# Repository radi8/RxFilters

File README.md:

# RxFilters

This is a first iteration of a set of high pass filters for a receiver. The filters are to be used in conjunction with the transmit low pass filters to form a bandpass filter which can be of variable width depending on the HP/LP combination selected. The advantage of this is that the Rx bandwidth can be wide (up to the Tx LP frequency) to enable skimming of frequencies up to the Tx frequency. I will be looking at diode switching of the filters in the future as this will give the option of developing smart filter switching to allow cross band operation etc. The receive can be a band set formed from a HP/LP combination and then when going to Tx the LP filter can be switched to match the Tx frequency and restored on receive.

This version is Relays only.

Notes:
The 1.8 MHz High Pass filter is in circuit by default all the time. In practise the broadcast signals are so strong that they can be received with the filter in. If full sensitivity operation in the broadcast and LF bands is desired then the filter is switched out and any appropriate filter switched in. Also with Hermes-Light the LNA gain can be reduced until clipping stops.

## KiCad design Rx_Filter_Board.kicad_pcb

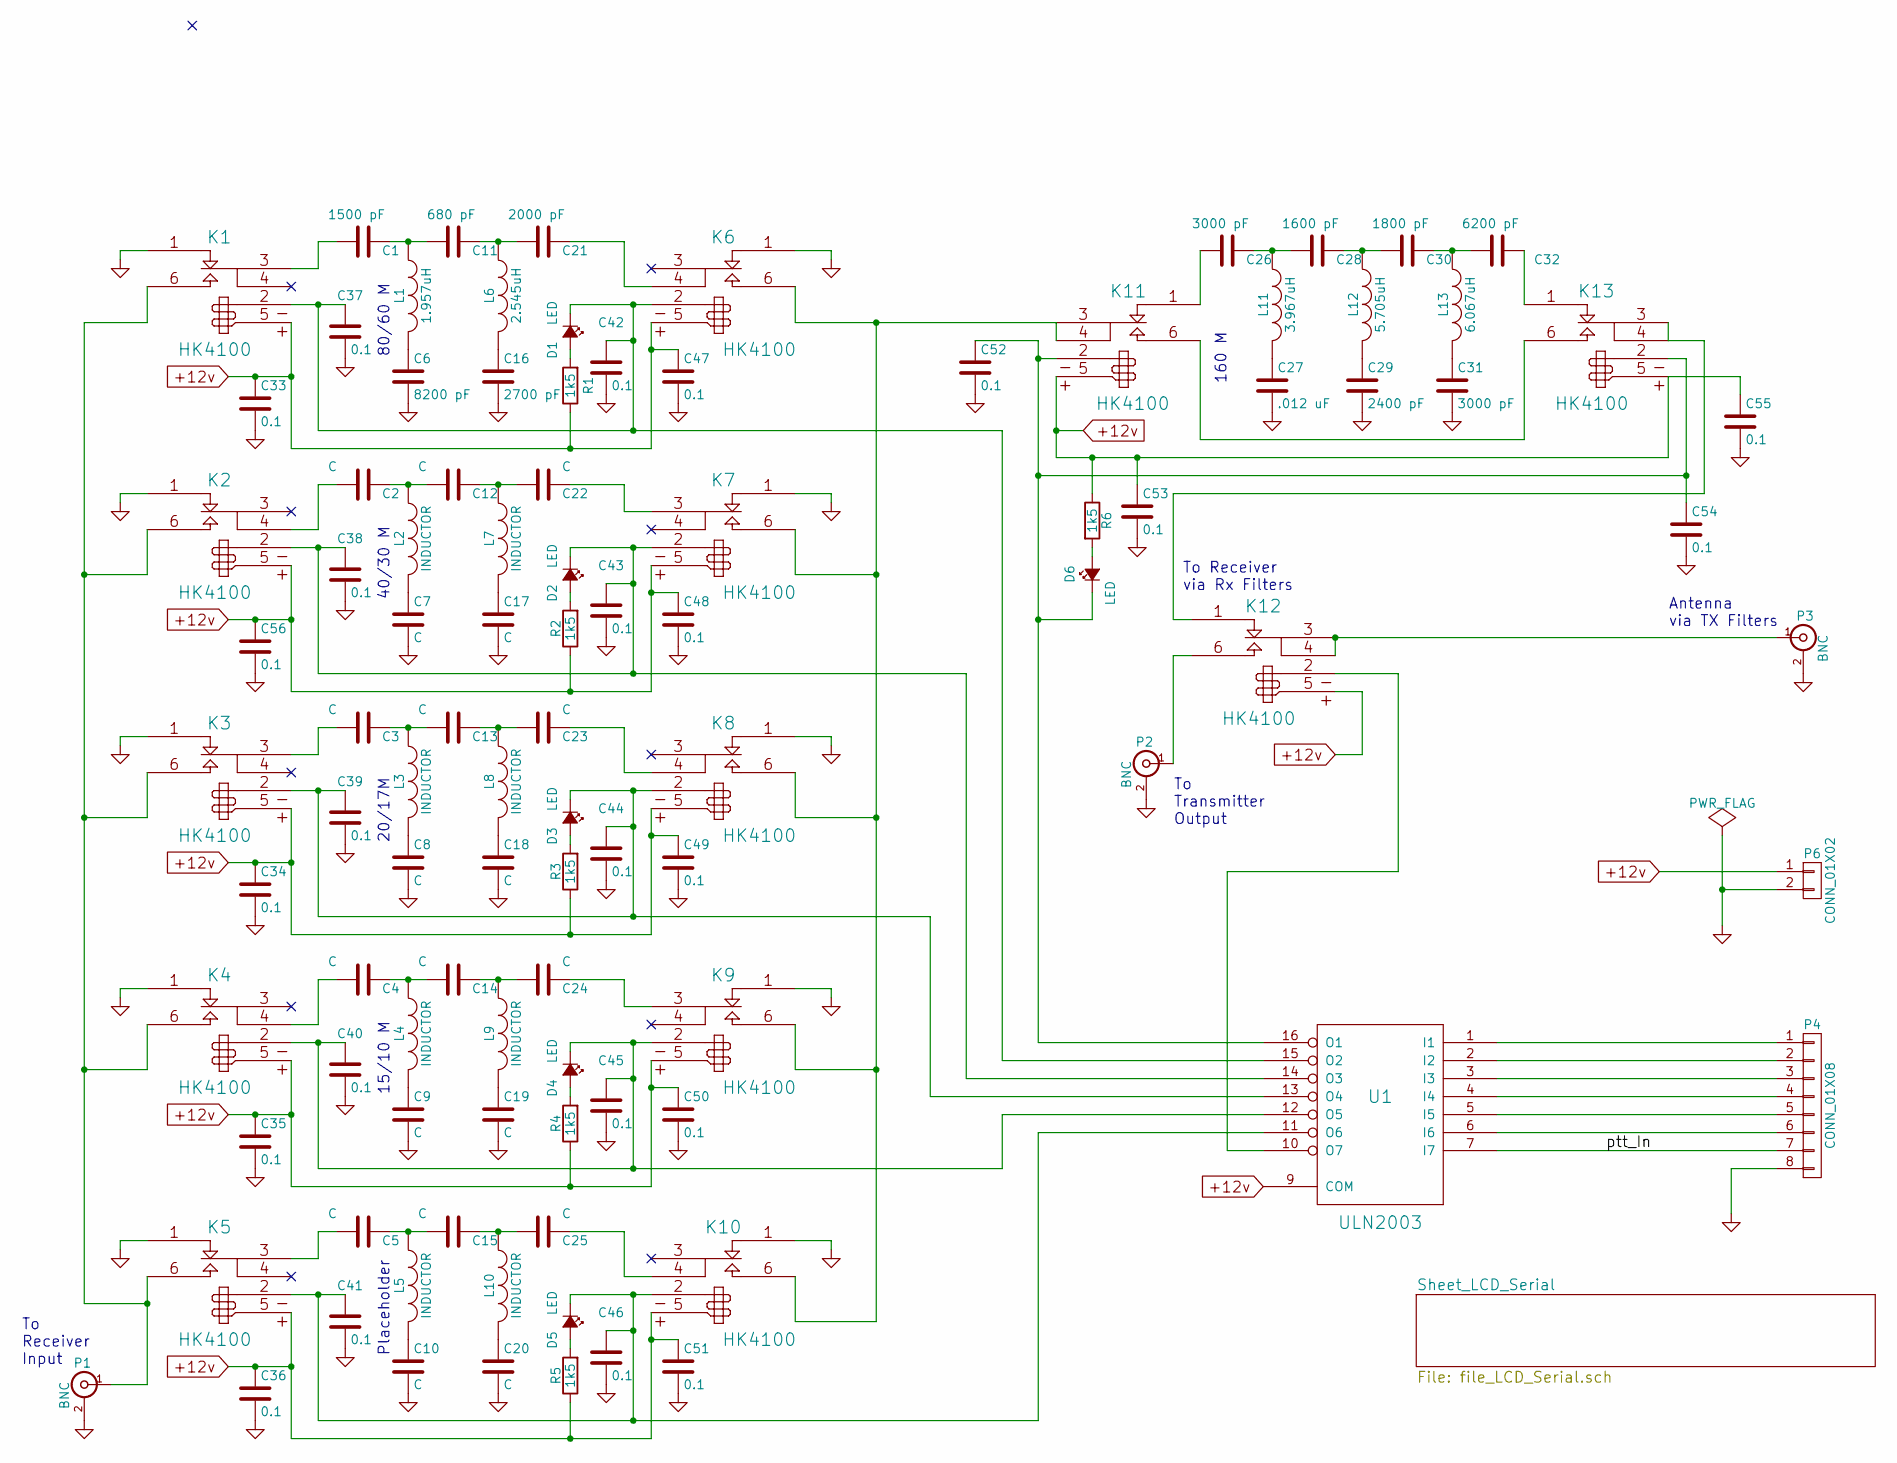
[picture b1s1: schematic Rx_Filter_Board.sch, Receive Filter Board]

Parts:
C1: 1500 pF; C_1206_HandSoldering
C2, C3, C4, C5, C7, C8, C9, C10, C12, C13, C14, C15, C17, C18, C19, C20, C22, C23, C24, C25: C; C_1206_HandSoldering
C6: 8200 pF; C_1206_HandSoldering
C11: 680 pF; C_1206_HandSoldering
C16: 2700 pF; C_1206_HandSoldering
C21: 2000 pF; C_1206_HandSoldering
C26, C31: 3000 pF; C_1206_HandSoldering
C27: .012 uF; C_1206_HandSoldering
C28: 1600 pF; C_1206_HandSoldering
C29: 2400 pF; C_1206_HandSoldering
C30: 1800 pF; C_1206_HandSoldering
C32: 6200 pF; C_1206_HandSoldering
C33, C34, C35, C36, C37, C38, C39, C40, C41, C42, C43, C44, C45, C46, C47, C48, C49, C50, C51, C52, C53, C54, C55, C56: 0.1; C_1206_HandSoldering
D1, D2, D3, D4, D5, D6: LED; LED_1206
K1, K2, K3, K4, K5, K6, K7, K8, K9, K10, K11, K12, K13: HK4100
L1: 1.957uH; Toroid_T37_Vertical
L2, L3, L4, L5, L7, L8, L9, L10: INDUCTOR; Toroid_T37_Vertical
L6: 2.545uH; Toroid_T37_Vertical
L11: 3.967uH; Toroid_T37_Vertical
L12: 5.705uH; Toroid_T37_Vertical
L13: 6.067uH; Toroid_T37_Vertical
P1, P2, P3: BNC; Pin_Header_Straight_1x02
P4: CONN_01X08; Pin_Header_Straight_1x08
P6: CONN_01X02; Pin_Header_Straight_1x02
R1, R2, R3, R4, R5, R6: 1k5; R_1206_HandSoldering
U1: ULN2003; DIP-16_W7.62mm_LongPads

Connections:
+12v: C33.1, C34.1, C35.1, C36.1, C47.1, C48.1, C49.1, C50.1, C51.1, C53.1, C55.1, C56.1, K1.5, K2.5, K3.5, K4.5, K5.5, K6.5, K7.5, K8.5, K9.5, K10.5, K11.5, K12.5, K13.5, P6.1, R1.1, R2.1, R3.1, R4.1, R5.1, R6.1, U1.9 (COM)
/ptt_In: P4.7, U1.7 (I7)
GND: C6.2, C7.2, C8.2, C9.2, C10.2, C16.2, C17.2, C18.2, C19.2, C20.2, C27.2, C29.2, C31.2, C33.2, C34.2, C35.2, C36.2, C37.2, C38.2, C39.2, C40.2, C41.2, C42.2, C43.2, C44.2, C45.2, C46.2, C47.2, C48.2, C49.2, C50.2, C51.2, C52.2, C53.2, C54.2, C55.2, C56.2, K1.1, K2.1, K3.1, K4.1, K5.1, K6.1, K7.1, K8.1, K9.1, K10.1, P1.2 (Ext), P2.2 (Ext), P3.2 (Ext), P4.8, P6.2, U1.8 (GND); also elsewhere on the board
unnamed: C1.1, C11.2, L1.1
unnamed: C1.2, K1.3
unnamed: C2.2, K2.4
unnamed: C3.2, K3.3
unnamed: C4.2, K4.4
unnamed: C5.2, K5.3
unnamed: C6.1, L1.2
unnamed: C7.1, L2.2
unnamed: C8.1, L3.2
unnamed: C9.1, L4.2
unnamed: C10.1, L5.2
unnamed: C11.1, C21.2, L6.1
unnamed: C12.1, C22.2, L7.1
unnamed: C2.1, C12.2, L2.1
unnamed: C13.1, C23.2, L8.1
unnamed: C3.1, C13.2, L3.1
unnamed: C14.1, C24.2, L9.1
unnamed: C4.1, C14.2, L4.1
unnamed: C15.1, C25.2, L10.1
unnamed: C5.1, C15.2, L5.1
unnamed: C16.1, L6.2
unnamed: C17.1, L7.2
unnamed: C18.1, L8.2
unnamed: C19.1, L9.2
unnamed: C20.1, L10.2
unnamed: C21.1, K6.4
unnamed: C22.1, K7.3
unnamed: C23.1, K8.4
unnamed: C24.1, K9.3
unnamed: C25.1, K10.4
unnamed: C26.1, C28.2, L11.1
unnamed: C26.2, K11.1
unnamed: C27.1, L11.2
unnamed: C28.1, C30.2, L12.1
unnamed: C29.1, L12.2
unnamed: C30.1, C32.2, L13.1
unnamed: C31.1, L13.2
unnamed: C32.1, K13.1
unnamed: C37.1, C42.1, D1.1 (K), K1.2, K6.2, U1.15 (O2)
unnamed: C38.1, C43.1, D2.1 (K), K2.2, K7.2, U1.14 (O3)
unnamed: C39.1, C44.1, D3.1 (K), K3.2, K8.2, U1.13 (O4)
unnamed: C40.1, C45.1, D4.1 (K), K4.2, K9.2, U1.12 (O5)
unnamed: C41.1, C46.1, D5.1 (K), K5.2, K10.2, U1.11 (O6)
unnamed: C52.1, C54.1, D6.1 (K), K11.2, K13.2, U1.16 (O1)
unnamed: D1.2 (A), R1.2
unnamed: D2.2 (A), R2.2
unnamed: D3.2 (A), R3.2
unnamed: D4.2 (A), R4.2
unnamed: D5.2 (A), R5.2
unnamed: D6.2 (A), R6.2
unnamed: K1.6, K2.6, K3.6, K4.6, K5.6, P1.1 (In)
unnamed: K6.6, K7.6, K8.6, K9.6, K10.6, K11.3, K11.4
unnamed: K11.6, K13.6
unnamed: K12.1, K13.3, K13.4
unnamed: K12.2, U1.10 (O7)
unnamed: K12.3, K12.4, P3.1 (In)
unnamed: K12.6, P2.1 (In)
unnamed: P4.1, U1.1 (I1)
unnamed: P4.2, U1.2 (I2)
unnamed: P4.3, U1.3 (I3)
unnamed: P4.4, U1.4 (I4)
unnamed: P4.5, U1.5 (I5)
unnamed: P4.6, U1.6 (I6)

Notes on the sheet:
To Receiver via Rx Filters
Antenna via TX Filters
160 M
40/30 M
20/17M
15/10 M
80/60 M
To Receiver Input
To Transmitter Output
Placeholder

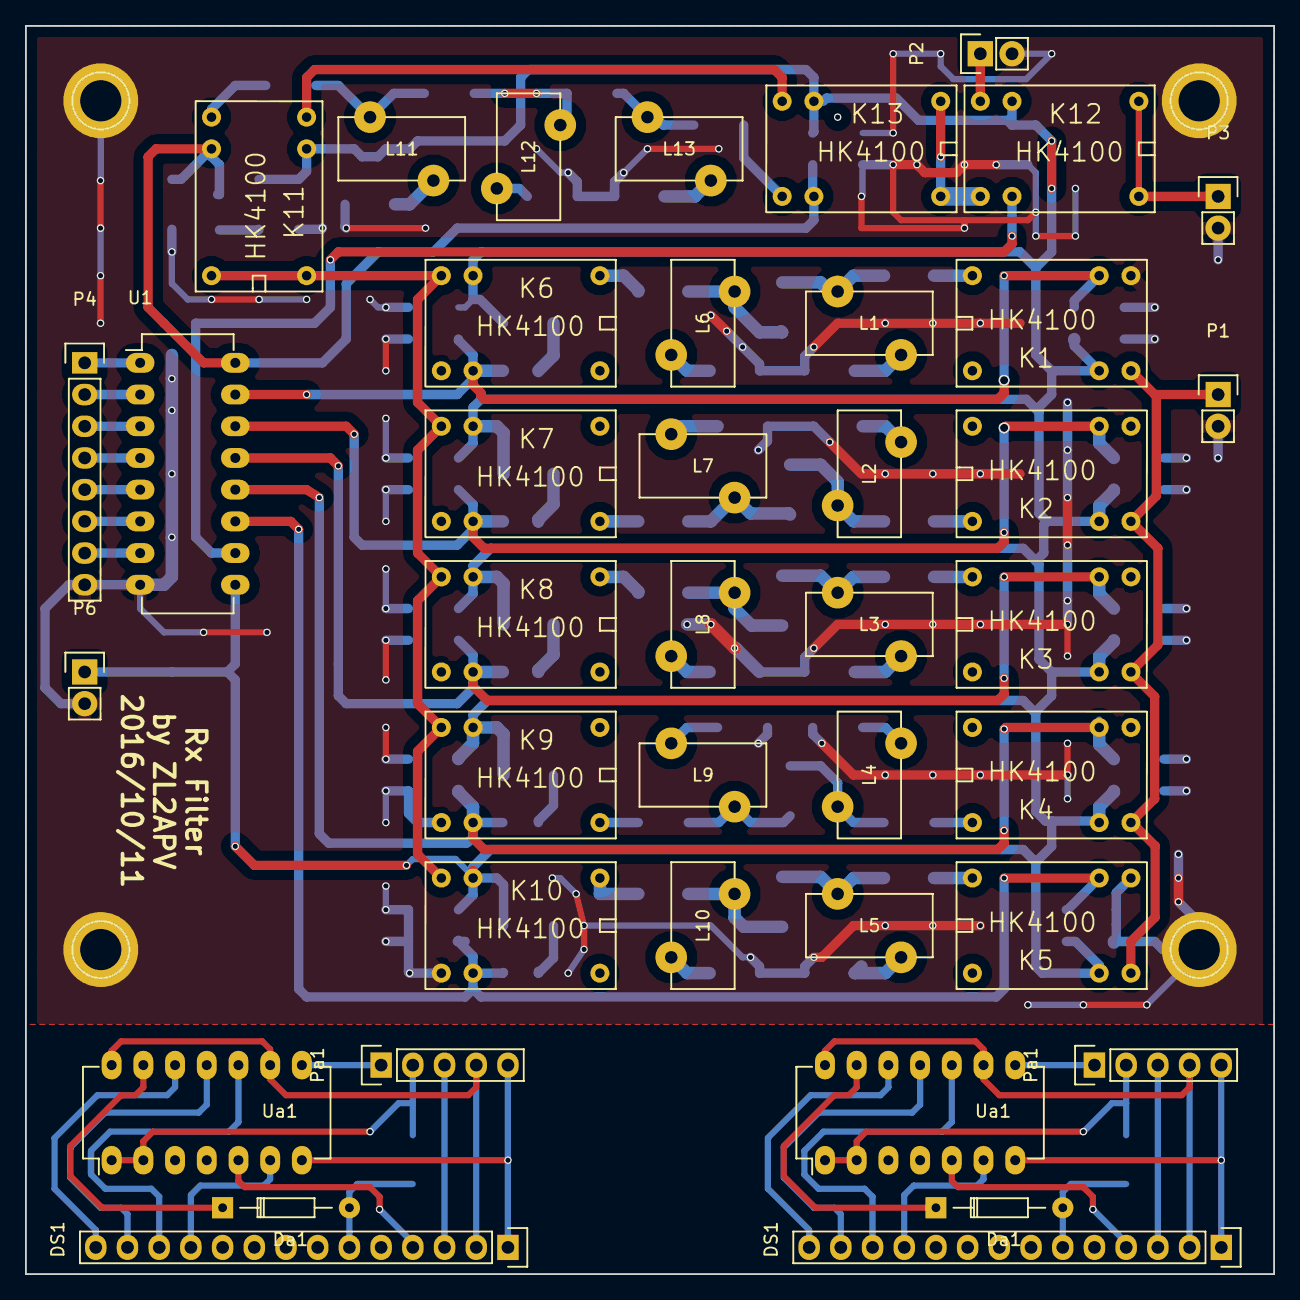
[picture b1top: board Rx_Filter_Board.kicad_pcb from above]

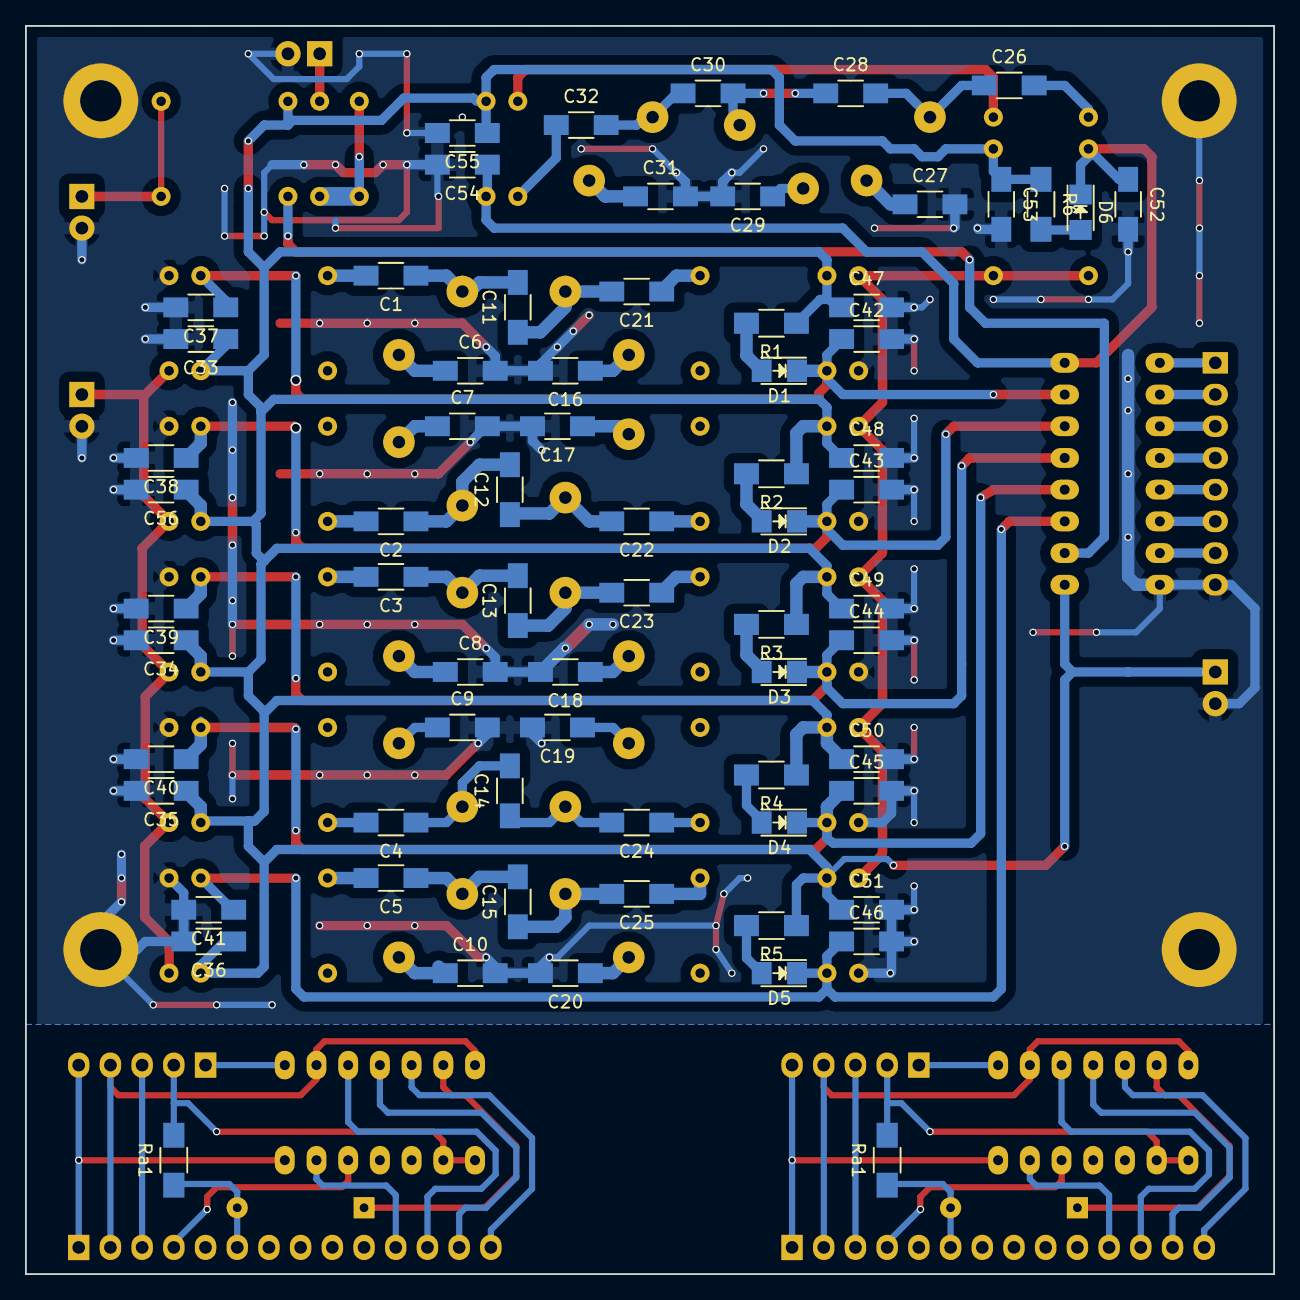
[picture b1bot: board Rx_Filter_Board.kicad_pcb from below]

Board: 2 copper layers, 100.0 x 100.0 mm, 114 parts (70 on the bottom side), 78 nets.

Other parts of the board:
CNR1, CNR2, CNR3: 1pin
CVR4: 1pin
DS1, DS1#2: LCD16X2; Pin_Header_Straight_1x14
Da1, Da1#2: 1N914; Diode_DO-35_SOD27_Horizontal_RM10
Pa1, Pa1#2: CONN_01X05; Pin_Header_Straight_1x05
Ra1, Ra1#2: 1k; R_1206_HandSoldering
Ua1, Ua1#2: 74LS164; DIP-14_W7.62mm_LongPads

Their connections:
GND: CNR1.1, CNR2.1, CNR3.1, CVR4.1; also elsewhere on the board
unnamed: DS1.1, DS1#2.1, Pa1.5, Pa1#2.5, Ua1.7, Ua1#2.7
unnamed: DS1.2, DS1#2.2, Pa1.4, Pa1#2.4, Ua1.9, Ua1.14, Ua1#2.9, Ua1#2.14
unnamed: DS1.3, DS1#2.3, Pa1.3, Pa1#2.3
unnamed: DS1.4, DS1#2.4, Ua1.5, Ua1#2.5
unnamed: DS1.6, DS1#2.6, Da1.2, Da1#2.2, Ra1.1, Ra1#2.1
unnamed: DS1.11, DS1#2.11, Ua1.6, Ua1#2.6
unnamed: DS1.12, DS1#2.12, Ua1.10, Ua1#2.10
unnamed: DS1.13, DS1#2.13, Ua1.11, Ua1#2.11
unnamed: DS1.14, DS1#2.14, Ua1.12, Ua1#2.12
unnamed: Da1.1, Da1#2.1, Ua1.13, Ua1#2.13
unnamed: Pa1.1, Pa1#2.1, Ua1.8, Ua1#2.8
unnamed: Pa1.2, Pa1#2.2, Ra1.2, Ra1#2.2, Ua1.1, Ua1.2, Ua1#2.1, Ua1#2.2

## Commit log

2016-09-30 First cut at filter circuit
2016-09-30 Some layout tweaks only
2016-10-06 Board at 1st layout stage
2016-10-06 Setting up ground plane
2016-10-07 A usable board at this point
2016-10-08 Saving home brew lazer board layout in branch Hbrew
2016-10-09 Filter progress
2016-10-10 Layout completed
2016-10-11 Final fabrication with LCD serial driver added
